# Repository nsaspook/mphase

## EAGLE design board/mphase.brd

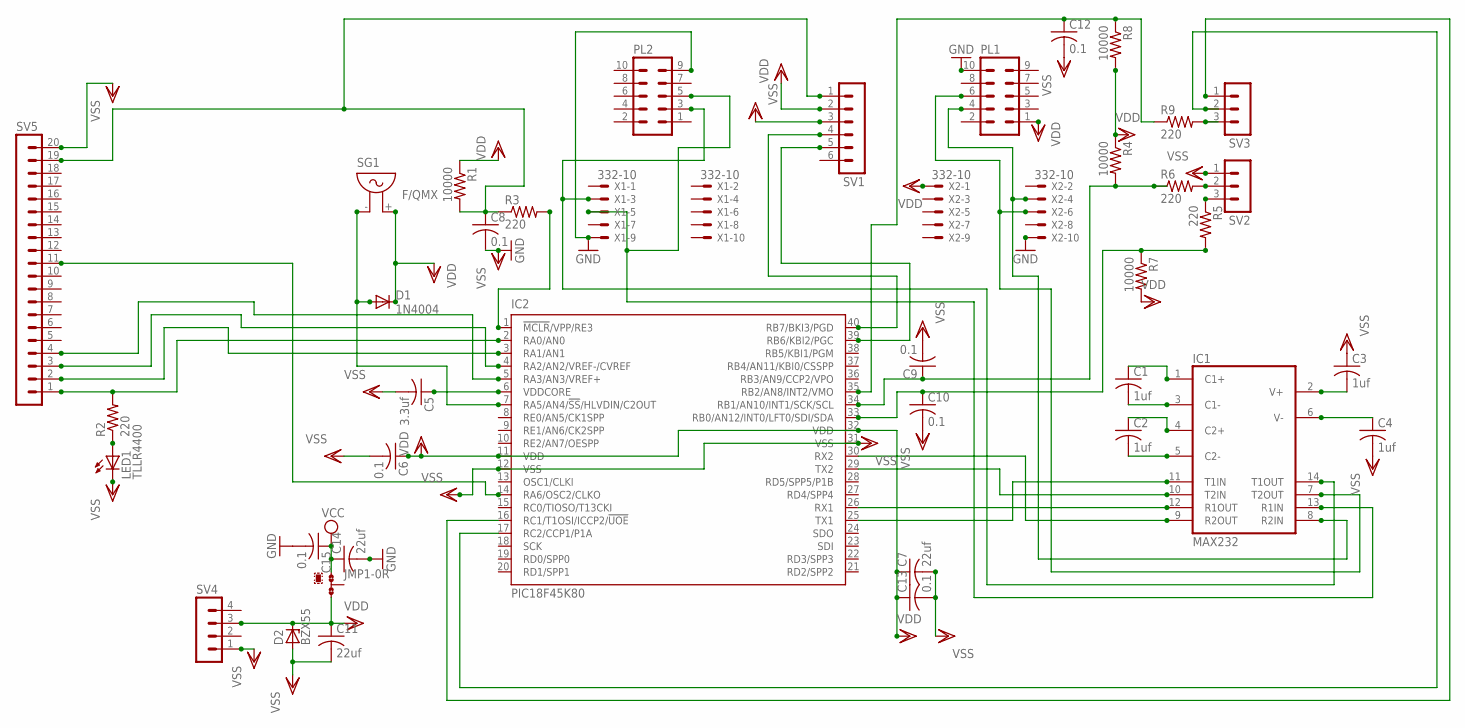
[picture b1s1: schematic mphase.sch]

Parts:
C1, C2, C3, C4: 1uf; C025-025X050
C5: 3.3uf; C025-025X050
C6, C15: 0.1; C025-025X050
C7, C11, C14: 22uf; C025-025X050
C8, C9, C10, C12, C13: 0.1; C025-024X044
D1: 1N4004; DO41-10
D2: BZX55; DO35Z10
IC1: MAX232; DIL16
IC2: PIC18F45K80; DIL40; MPN PIC18F45K80
JMP1: 0R-JUMPA; A0R-JMP
LED1: TLLR4400; LED3MM
PL1, PL2: 10H
R1, R4, R7, R8: 10000; 0204V
R2, R3, R5, R6, R9: 220; 0204V
SG1: F/QMX
SV1: MA06-1
SV2, SV3: MA03-1
SV4: MA04-1
SV5: MA20-1
X1, X2: 332-10

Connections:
GND: C8.2, C14.2, C15.2, IC1.15 (GND), PL1.10, PL2.9, X1.9, X2.10
unnamed: C1.2, IC1.3 (C1-)
unnamed: C2.2, IC1.5 (C2-)
unnamed: C2.1, IC1.4 (C2+)
unnamed: C1.1, IC1.1 (C1+)
unnamed: C3.2, IC1.2 (V+)
unnamed: C4.1, IC1.6 (V-)
unnamed: D1.A, IC2.7 (RA5/AN4/!SS!/HLVDIN/C2OUT), SG1.- (1)
unnamed: C8.1, R1.2, R3.1, SV1.1, SV5.19
unnamed: C5.1, IC2.6 (VDDCORE)
unnamed: IC1.10 (T2IN), IC2.29 (TX2)
unnamed: IC1.11 (T1IN), IC2.25 (TX1)
unnamed: IC1.12 (R1OUT), IC2.26 (RX1)
unnamed: IC1.9 (R2OUT), IC2.30 (RX2)
unnamed: IC2.1 (!MCLR!/VPP/RE3), R3.2
unnamed: IC2.2 (RA0/AN0), R2.2, SV5.1
unnamed: IC1.7 (T2OUT), PL1.6, X2.6
unnamed: IC1.8 (R2IN), PL1.4, X2.4
unnamed: LED1.A, R2.1
unnamed: IC1.14 (T1OUT), PL2.3, X1.3
unnamed: IC1.13 (R1IN), PL2.5, X1.5
unnamed: C9.1, IC2.34 (RB1/AN10/INT1/SCK/SCL), R4.2, R6.1
unnamed: C10.1, IC2.33 (RB0/AN12/INT0/LFT0/SDI/SDA), R5.2, R7.1
unnamed: IC2.3 (RA1/AN1), SV5.2
unnamed: R6.2, SV2.2
unnamed: R5.1, SV2.3
unnamed: IC2.4 (RA2/AN2/VREF-/CVREF), SV5.3
unnamed: IC2.5 (RA3/AN3/VREF+), SV5.4
unnamed: C12.1, IC2.35 (RB2/AN8/INT2/VMO), R8.1, R9.1
unnamed: IC2.40 (RB7/BKI3/PGD), SV1.4
unnamed: IC2.14 (RA6/OSC2/CLKO), SV5.11
unnamed: R9.2, SV3.3
unnamed: IC2.39 (RB6/KBI2/PGC), SV1.5
unnamed: IC2.16 (RC1/T1OSI/ICCP2/!UOE), SV3.1
unnamed: IC2.17 (RC2/CCP1/P1A), SV3.2
VCC: C14.1, C15.1, IC1.16 (VCC), JMP1.1
VDD: C6.1, C7.1, C11.1, C13.1, D1.C, D2.C, IC2.11 (VDD), IC2.32 (VDD), JMP1.3, PL1.1, R1.1, R4.1, R7.2, R8.2, SG1.+ (2), SV1.2, SV4.3, X2.1
VSS: C3.1, C4.2, C5.2, C6.2, C7.2, C9.2, C10.2, C11.2, C12.2, C13.2, D2.A, IC2.12 (VSS), IC2.31 (VSS), LED1.K (C), SV1.3, SV2.1, SV4.1, SV5.20

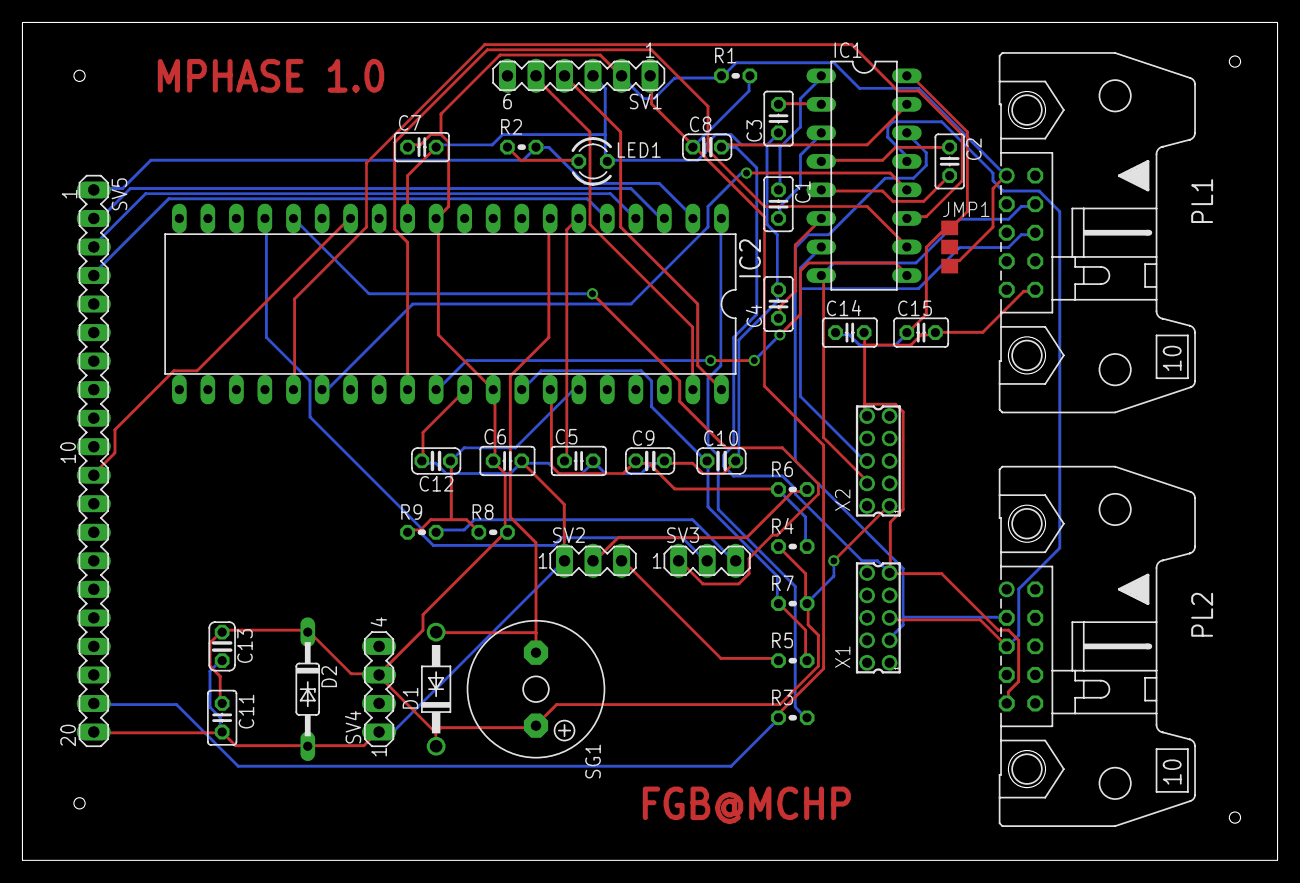
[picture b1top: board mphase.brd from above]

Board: 2 copper layers, 111.7 x 74.6 mm, 40 parts (0 on the bottom side), 38 nets.

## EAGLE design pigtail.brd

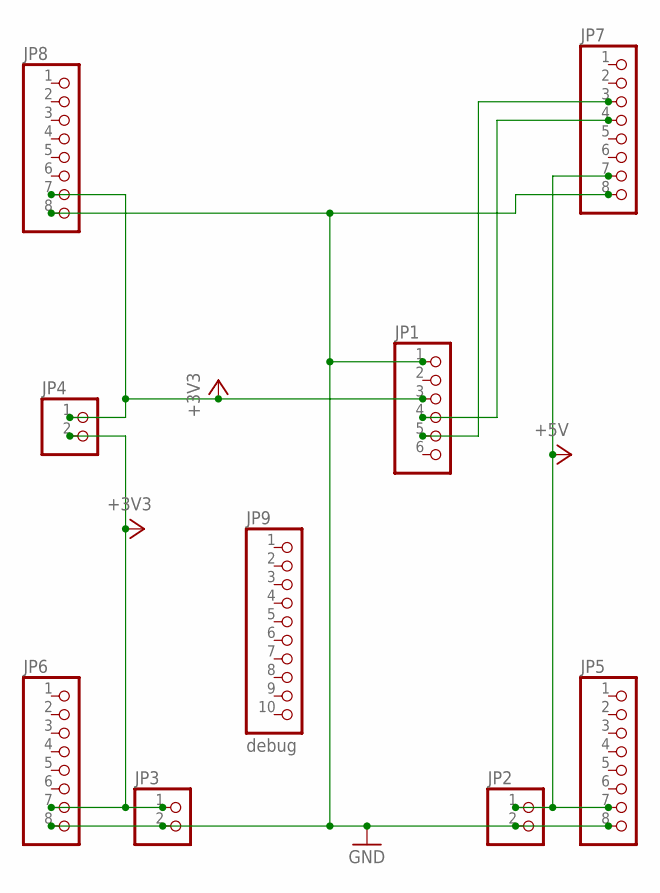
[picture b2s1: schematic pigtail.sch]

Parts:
JP1: PINHD-1X6; 1X06
JP2, JP3, JP4: PINHD-1X2; 1X02
JP5, JP6, JP7, JP8: PINHD-1X8; 1X08
JP9: debug; 1X10

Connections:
+3V3: JP1.3, JP3.1, JP4.1, JP4.2, JP6.7, JP8.7
+5V: JP2.1, JP5.7, JP7.7
GND: JP1.1, JP2.2, JP3.2, JP5.8, JP6.8, JP7.8, JP8.8
unnamed: JP1.4, JP7.4
unnamed: JP1.5, JP7.3

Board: 2 copper layers, 9 parts (0 on the bottom side), 5 nets, no tracks yet.

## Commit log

2018-10-09 update code
2018-10-25 program updates
2019-10-03 update board
